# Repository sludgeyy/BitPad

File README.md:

# BitPad
My submission for the Hackclub Stardance challenge's Hackpad mission.
Instead of each button executing a command, each button is a bit. This means you send a sequence of bits (e.g. 0110), allowing for a lot more possible commands.
WIP

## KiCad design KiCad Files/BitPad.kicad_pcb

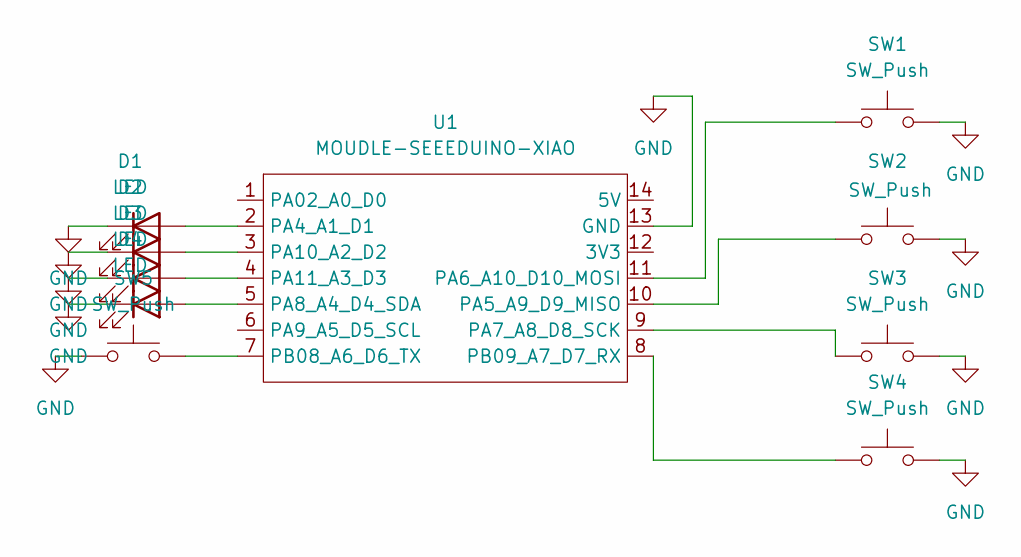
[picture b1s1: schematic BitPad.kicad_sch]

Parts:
D1, D2, D3, D4: LED; D_0201_0603Metric
SW1, SW2, SW3, SW4: SW_Push; SW_Cherry_MX_1.00u_PCB
SW5: SW_Push; SW_TH_Tactile_Omron_B3F-100x
U1: MOUDLE-SEEEDUINO-XIAO; XIAO-Generic-Hybrid-14P-2.54-21X17.8MM

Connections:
GND: D1.1 (K), D2.1 (K), D3.1 (K), D4.1 (K), SW1.2, SW2.2, SW3.2, SW4.2, SW5.1, U1.13 (GND)
unnamed: D1.2 (A), U1.2 (PA4_A1_D1)
unnamed: D2.2 (A), U1.3 (PA10_A2_D2)
unnamed: D3.2 (A), U1.4 (PA11_A3_D3)
unnamed: D4.2 (A), U1.5 (PA8_A4_D4_SDA)
unnamed: SW2.1, U1.10 (PA5_A9_D9_MISO)
unnamed: SW1.1, U1.11 (PA6_A10_D10_MOSI)
unnamed: SW3.1, U1.9 (PA7_A8_D8_SCK)
unnamed: SW5.2, U1.7 (PB08_A6_D6_TX)
unnamed: SW4.1, U1.8 (PB09_A7_D7_RX)

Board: 2 copper layers, 10 parts (0 on the bottom side), 10 nets, no tracks yet.

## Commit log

2026-06-28 Initialize README with project details
    Added project description and purpose.
2026-06-28 Schematic and PCB KiCad files
2026-06-29 updated the kicad files
2026-06-29 added .step file for the case
    keep in mind that this .step is still the first build and not done
2026-06-29 added the updated kicad files
2026-06-29 Deleteted wrong directoy
2026-06-29 Deleted wrong file
